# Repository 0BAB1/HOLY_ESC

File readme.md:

# HOLY ESC

My effort to bring an open source, closed loop ESC to life.

From hardware to firmware.

> This image was edited using AI to remove stickers that were bloating the image.

You can order the **FULL BUILD** in a couple of click right : (Todo : add link once project post is approved)

> [!NOTE]  
> This ESC was featured in one of my youtube videos. You may be searching for the AtMega based firmware and perfboard BOM / Schematics. I did not put these here as the design worked but is not reliable. You can open an issue if you really want it and I'll add it to some "deprecated" folder in the repo.

## THE PROJECT

The HOLY ESC is a BACK EMF based ESC, theorically able to be loaded up to 25Amps and more. But it serve educational purupses and has not be stress tested for any applications yet.

It was designed on KiCad 9 and aims at using cheap components to make the design accessible to all.

This design target drones and is planned to be tested on such applications soon.

Here are views of the PCB layers:

## Usage

### Hardware

The hardware folder contains the KiCad9 files that you can open and modify as you like for your own needs, as long as you respect the project licence at the root of this repo.

### Sofware

The sofware part is a bit more tricky.

If you get the board manufactured, you will need to load a firmware on it. In this repo, I distribute AM32 binaries made specifically for this ESC.

Here is the procedure to start spinning a motor:

**1. Connect the HOLY ESC to your host PC**

First you'll need to connect the ESC's STM32 to a host computer.

So you'll need :

- A 15V or so power supply to power the board.
- A Stlink V2 (or any clone should work as long as it has SWD)
- Download STM32CUBE programmer software

So connect the ESC to your power supply on the dedicated pads (Labeled "+" and "-" on the back of the PCB), I suggest limiting max current to 1 Amp in case a fault arises. Red LEDS should turn on, indicating a good supply of voltage into the board.

Connect the ESC SWD headers to you STLINK

And plug it into you computer.

Launch STMCUBE Programmer, click connect and it should recognze the MCU on the ESC board.

At this point you can also connect a BLDC motor on the 3 phases pads using solder (labeled A; B & C on the back of the board).

**2. Load the Firmware**

To load the firmware, you have to load a coouple things. The procedure is describe here pretty well :

[https://github-wiki-see.page/m/AlkaMotors/AM32-MultiRotor-ESC-firmware/wiki/Memory-Layout-for-flashing-with-a-St-link?utm_source=chatgpt.com](https://github-wiki-see.page/m/AlkaMotors/AM32-MultiRotor-ESC-firmware/wiki/Memory-Layout-for-flashing-with-a-St-link?utm_source=chatgpt.com)

You can use STMCube's "Erasing and Programming" tab to select a binary and load it to a specified address. Just load each binary at the right address and you should be good to go.

> To verify if you corecty modified a memory region, you can use the "Memory and File editing tab" to read a specific memory region, to check if it changed from the default values.

Bootloading and eeprom binaries are found in the page linked above. **You will find the specific binary built for this specific board in `./software/`**

> [!TIP]  
> If you are hardstuck on trying to lad a firmware, you can open an issue to get support.

Once the firmware is succesfully loaded, connect a BLDC motor to the phases pads (labeled A, B and C at the back of the PCB) using solder. Turn on your power supply (with STLINKV2 connected to PC or completely off the board to avoid asserting reset) and you should ear 3 beeps, indicating the motor is ready to armed !

Congratulations ! Now to spin a motor, you can use an arduino + voltage divider as a quick test, like I did in the video (use an LLM to write the arming sequence and speed command PWM generation) or use a servo tester / real flight controller.

> [!INFO]
> Telemetry feedback and AM32 monitoring tools not tested yet

## Future Work

- Replace the STM32F051 with a cheaper and more available package / version. (right now its 5+$ !!!! When I made the design it was like for 3-4$ MAX before going out of stock on LCSC)
- Add vias under the FETs as well. I did not initially did so to avoid assembly problems but adding a few vias on the mosfet pad should drastically increase Amperage tolerance.

## Inspirations & Thanks

A big thank you to these actors, who were a great source of inspiration in my learning and designing process !

- [The Engineering Techie](https://www.youtube.com/watch?v=1ThH9cA4eWE&t=8s)
- [Electronoobs](https://www.youtube.com/watch?v=8LXPcJD6hEA)
- [10x Aero](https://github.com/10x-Aero/ESC-Development-Board/tree/main)
- AM32 Community and posts

## Self Promotion

- The youtube channel which I featured this project on : [BRH YOUTUBE](https://www.youtube.com/@BRH_SoC)
- My Blog : [Blog Link](https://hugobrh.dev)

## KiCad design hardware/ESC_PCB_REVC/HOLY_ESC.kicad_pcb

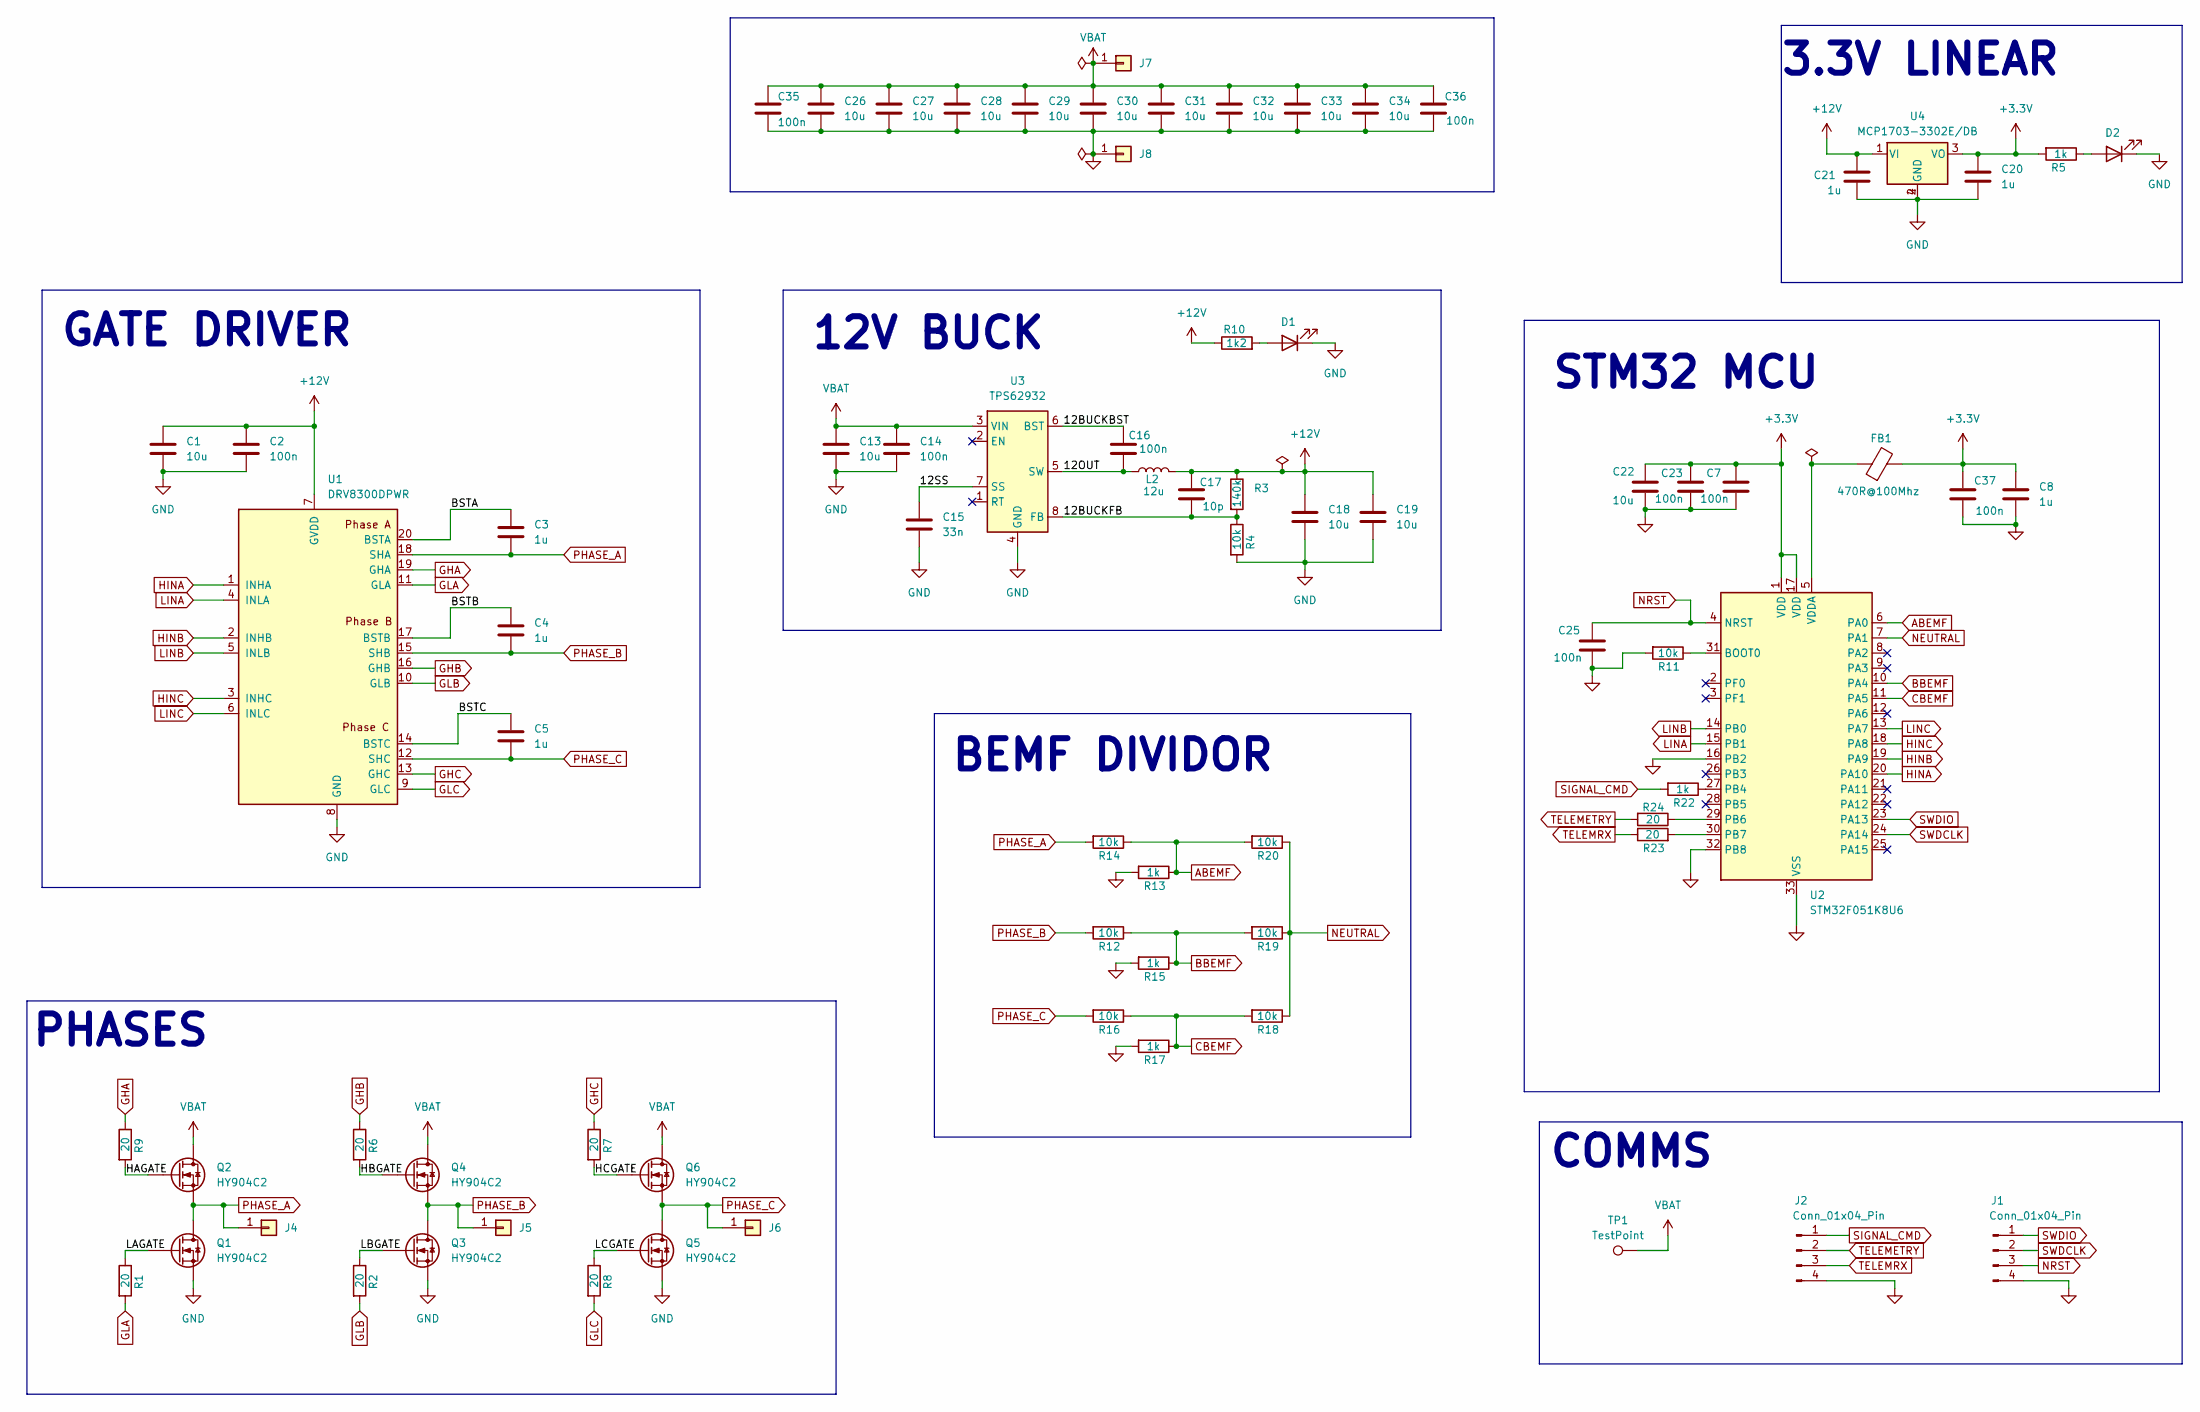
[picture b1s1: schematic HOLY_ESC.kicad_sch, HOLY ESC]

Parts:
C1, C13, C18, C19, C22, C26, C27, C28, C29, C30, C31, C32, C33, C34: 10u; C_1206_3216Metric_Pad1.33x1.80mm_HandSolder; MPN CL31A106KBHNNNE; LCSC C13585
C2, C7, C14, C16, C23, C25, C35, C36, C37: 100n; C_0603_1608Metric_Pad1.08x0.95mm_HandSolder; MPN CL10B104KB8NNNC; LCSC C1591
C3, C4, C5, C8, C20, C21: 1u; C_0805_2012Metric_Pad1.18x1.45mm_HandSolder; MPN CL21B105KBFNNNE; LCSC C28323
C15: 33n; C_0603_1608Metric_Pad1.08x0.95mm_HandSolder; MPN CL10B333KB8NNNC; LCSC C21117
C17: 10p; C_0603_1608Metric_Pad1.08x0.95mm_HandSolder; MPN CL10C100JB8NNNC; LCSC C1634
D1, D2: RED; LED_0603_1608Metric_Pad1.05x0.95mm_HandSolder; MPN YLED0603R; LCSC C19171390
FB1: 470R@100Mhz; L_0603_1608Metric_Pad1.05x0.95mm_HandSolder; MPN BLM18PG471SN1D; LCSC C97853
J1, J2: Conn_01x04_Pin; PinHeader_1x04_P2.54mm_Vertical; LCSC C32713270
J4, J5, J6, J7, J8: BatteryPad
L2: 12u; L_6.3x6.3_H3; MPN MNR6045T120MT; LCSC C20612509
Q1, Q2, Q3, Q4, Q5, Q6: HY904C2; DFN-8_L5.9-W5.2-P1.27-LS6.2-BL; MPN HY1904C2; LCSC C358116
R1, R2, R6, R7, R8, R9, R23, R24: 20; R_0603_1608Metric_Pad0.98x0.95mm_HandSolder; MPN 0603WAF200JT5E; LCSC C22950
R3: 140k; R_0603_1608Metric_Pad0.98x0.95mm_HandSolder; MPN FRC0603F1403TS; LCSC C2933144
R4, R11, R12, R14, R16, R18, R19, R20: 10k; R_0603_1608Metric_Pad0.98x0.95mm_HandSolder; MPN RT0603BRD0710KL; LCSC C95204
R5, R13, R15, R17, R22: 1k; R_0603_1608Metric_Pad0.98x0.95mm_HandSolder; MPN FRC0603F1001TS; LCSC C2907002
R10: 1k2; R_0603_1608Metric_Pad0.98x0.95mm_HandSolder; MPN FRC0603J122 TS; LCSC C2907081
TP1: TestPoint; PinHeader_1x01_P2.54mm_Vertical
U1: DRV8300DPWR; TSSOP-20_4.4x6.5mm_P0.65mm; LCSC C3036056
U2: STM32F051K8U6; QFN-32-1EP_5x5mm_P0.5mm_EP3.45x3.45mm; LCSC C72339
U3: TPS62932; SOT-583-8; MPN TPS62932DRLR; LCSC C3032935
U4: MCP1703-3302E/DB; SOT-223; MPN MCP1703-3302E/DB; LCSC C512091

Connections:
+3.3V: C7.1, C8.1, C20.1, C22.1, C23.1, C37.1, FB1.2, R5.2, U2.1 (VDD), U2.17 (VDD), U4.3 (VO)
+12V: C1.1, C2.1, C17.1, C18.1, C19.1, C21.1, L2.2, R3.1, R10.1, U1.7 (GVDD), U4.1 (VI)
/12BUCKBST: C16.1, U3.6 (BST)
/12BUCKFB: C17.2, R3.2, R4.1, U3.8 (FB)
/12OUT: C16.2, L2.1, U3.5 (SW)
/12SS: C15.1, U3.7 (SS)
/<NO NET>: FB1.1, U2.5 (VDDA)
/BSTA: C3.1, U1.20 (BSTA)
/BSTB: C4.1, U1.17 (BSTB)
/BSTC: C5.1, U1.14 (BSTC)
/HAGATE: Q2.4 (Gate), R9.2
/HBGATE: Q4.4 (Gate), R6.2
/HCGATE: Q6.4 (Gate), R7.2
/LAGATE: Q1.4 (Gate), R1.1
/LBGATE: Q3.4 (Gate), R2.1
/LCGATE: Q5.4 (Gate), R8.1
ABEMF: R13.1, R14.1, R20.2, U2.6 (PA0)
BBEMF: R12.1, R15.1, R19.2, U2.10 (PA4)
CBEMF: R16.1, R17.1, R18.2, U2.11 (PA5)
GHA: R9.1, U1.19 (GHA)
GHB: R6.1, U1.16 (GHB)
GHC: R7.1, U1.13 (GHC)
GLA: R1.2, U1.11 (GLA)
GLB: R2.2, U1.10 (GLB)
GLC: R8.2, U1.9 (GLC)
GND: C1.2, C2.2, C7.2, C8.2, C13.2, C14.2, C15.2, C18.2, C19.2, C20.2, C21.2, C22.2, C23.2, C25.2, C26.2, C27.2, C28.2, C29.2, C30.2, C31.2, C32.2, C33.2, C34.2, C35.2, C36.2, C37.2, D1.1 (K), D2.1 (K), J1.4, J2.4, J8.1, Q1.1 (Source), Q1.2 (Source), Q1.3 (Source), Q3.1 (Source), Q3.2 (Source), Q3.3 (Source), Q5.1 (Source), Q5.2 (Source), Q5.3 (Source), R4.2, R11.2, R13.2, R15.2, R17.2, U1.8 (GND), U2.16 (PB2), U2.32 (PB8), U2.33 (VSS), U3.4 (GND), U4.2 (GND), U4.4 (GND)
HINA: U1.1 (INHA), U2.20 (PA10)
HINB: U1.2 (INHB), U2.19 (PA9)
HINC: U1.3 (INHC), U2.18 (PA8)
LINA: U1.4 (INLA), U2.15 (PB1)
LINB: U1.5 (INLB), U2.14 (PB0)
LINC: U1.6 (INLC), U2.13 (PA7)
NEUTRAL: R18.1, R19.1, R20.1, U2.7 (PA1)
NRST: C25.1, J1.3, U2.4 (NRST)
unnamed: D1.2 (A), R10.2
unnamed: D2.2 (A), R5.1
unnamed: R11.1, U2.31 (BOOT0)
unnamed: R22.1, U2.27 (PB4)
unnamed: R23.1, U2.29 (PB6)
unnamed: R24.2, U2.30 (PB7)
PHASE_A: C3.2, J4.1, Q1.5 (Drain), Q1.6 (Drain), Q1.7 (Drain), Q1.8 (Drain), Q1.9 (Drain), Q2.1 (Source), Q2.2 (Source), Q2.3 (Source), R14.2, U1.18 (SHA)
PHASE_B: C4.2, J5.1, Q3.5 (Drain), Q3.6 (Drain), Q3.7 (Drain), Q3.8 (Drain), Q3.9 (Drain), Q4.1 (Source), Q4.2 (Source), Q4.3 (Source), R12.2, U1.15 (SHB)
PHASE_C: C5.2, J6.1, Q5.5 (Drain), Q5.6 (Drain), Q5.7 (Drain), Q5.8 (Drain), Q5.9 (Drain), Q6.1 (Source), Q6.2 (Source), Q6.3 (Source), R16.2, U1.12 (SHC)
SIGNAL_CMD: J2.1, R22.2
SWDCLK: J1.2, U2.24 (PA14)
SWDIO: J1.1, U2.23 (PA13)
TELEMETRY: J2.2, R23.2
TELEMRX: J2.3, R24.1
VBAT: C13.1, C14.1, C26.1, C27.1, C28.1, C29.1, C30.1, C31.1, C32.1, C33.1, C34.1, C35.1, C36.1, J7.1, Q2.5 (Drain), Q2.6 (Drain), Q2.7 (Drain), Q2.8 (Drain), Q2.9 (Drain), Q4.5 (Drain), Q4.6 (Drain), Q4.7 (Drain), Q4.8 (Drain), Q4.9 (Drain), Q6.5 (Drain), Q6.6 (Drain), Q6.7 (Drain), Q6.8 (Drain), Q6.9 (Drain), TP1.1, U3.3 (VIN)

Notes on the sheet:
GATE DRIVER
BEMF DIVIDOR
STM32 MCU
12V BUCK
PHASES
3.3V LINEAR
COMMS

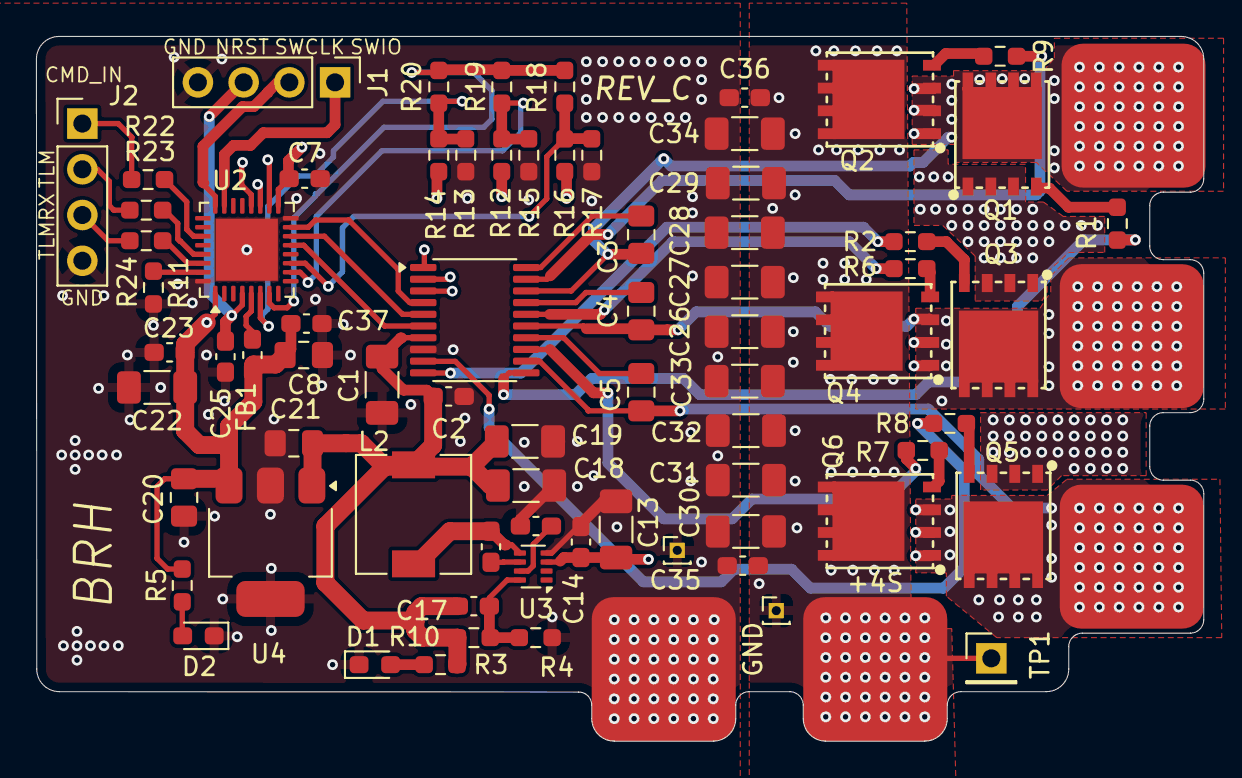
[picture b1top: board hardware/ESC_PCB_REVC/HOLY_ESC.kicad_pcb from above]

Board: 4 copper layers, 64.8 x 39.2 mm, 76 parts (0 on the bottom side), 49 nets.

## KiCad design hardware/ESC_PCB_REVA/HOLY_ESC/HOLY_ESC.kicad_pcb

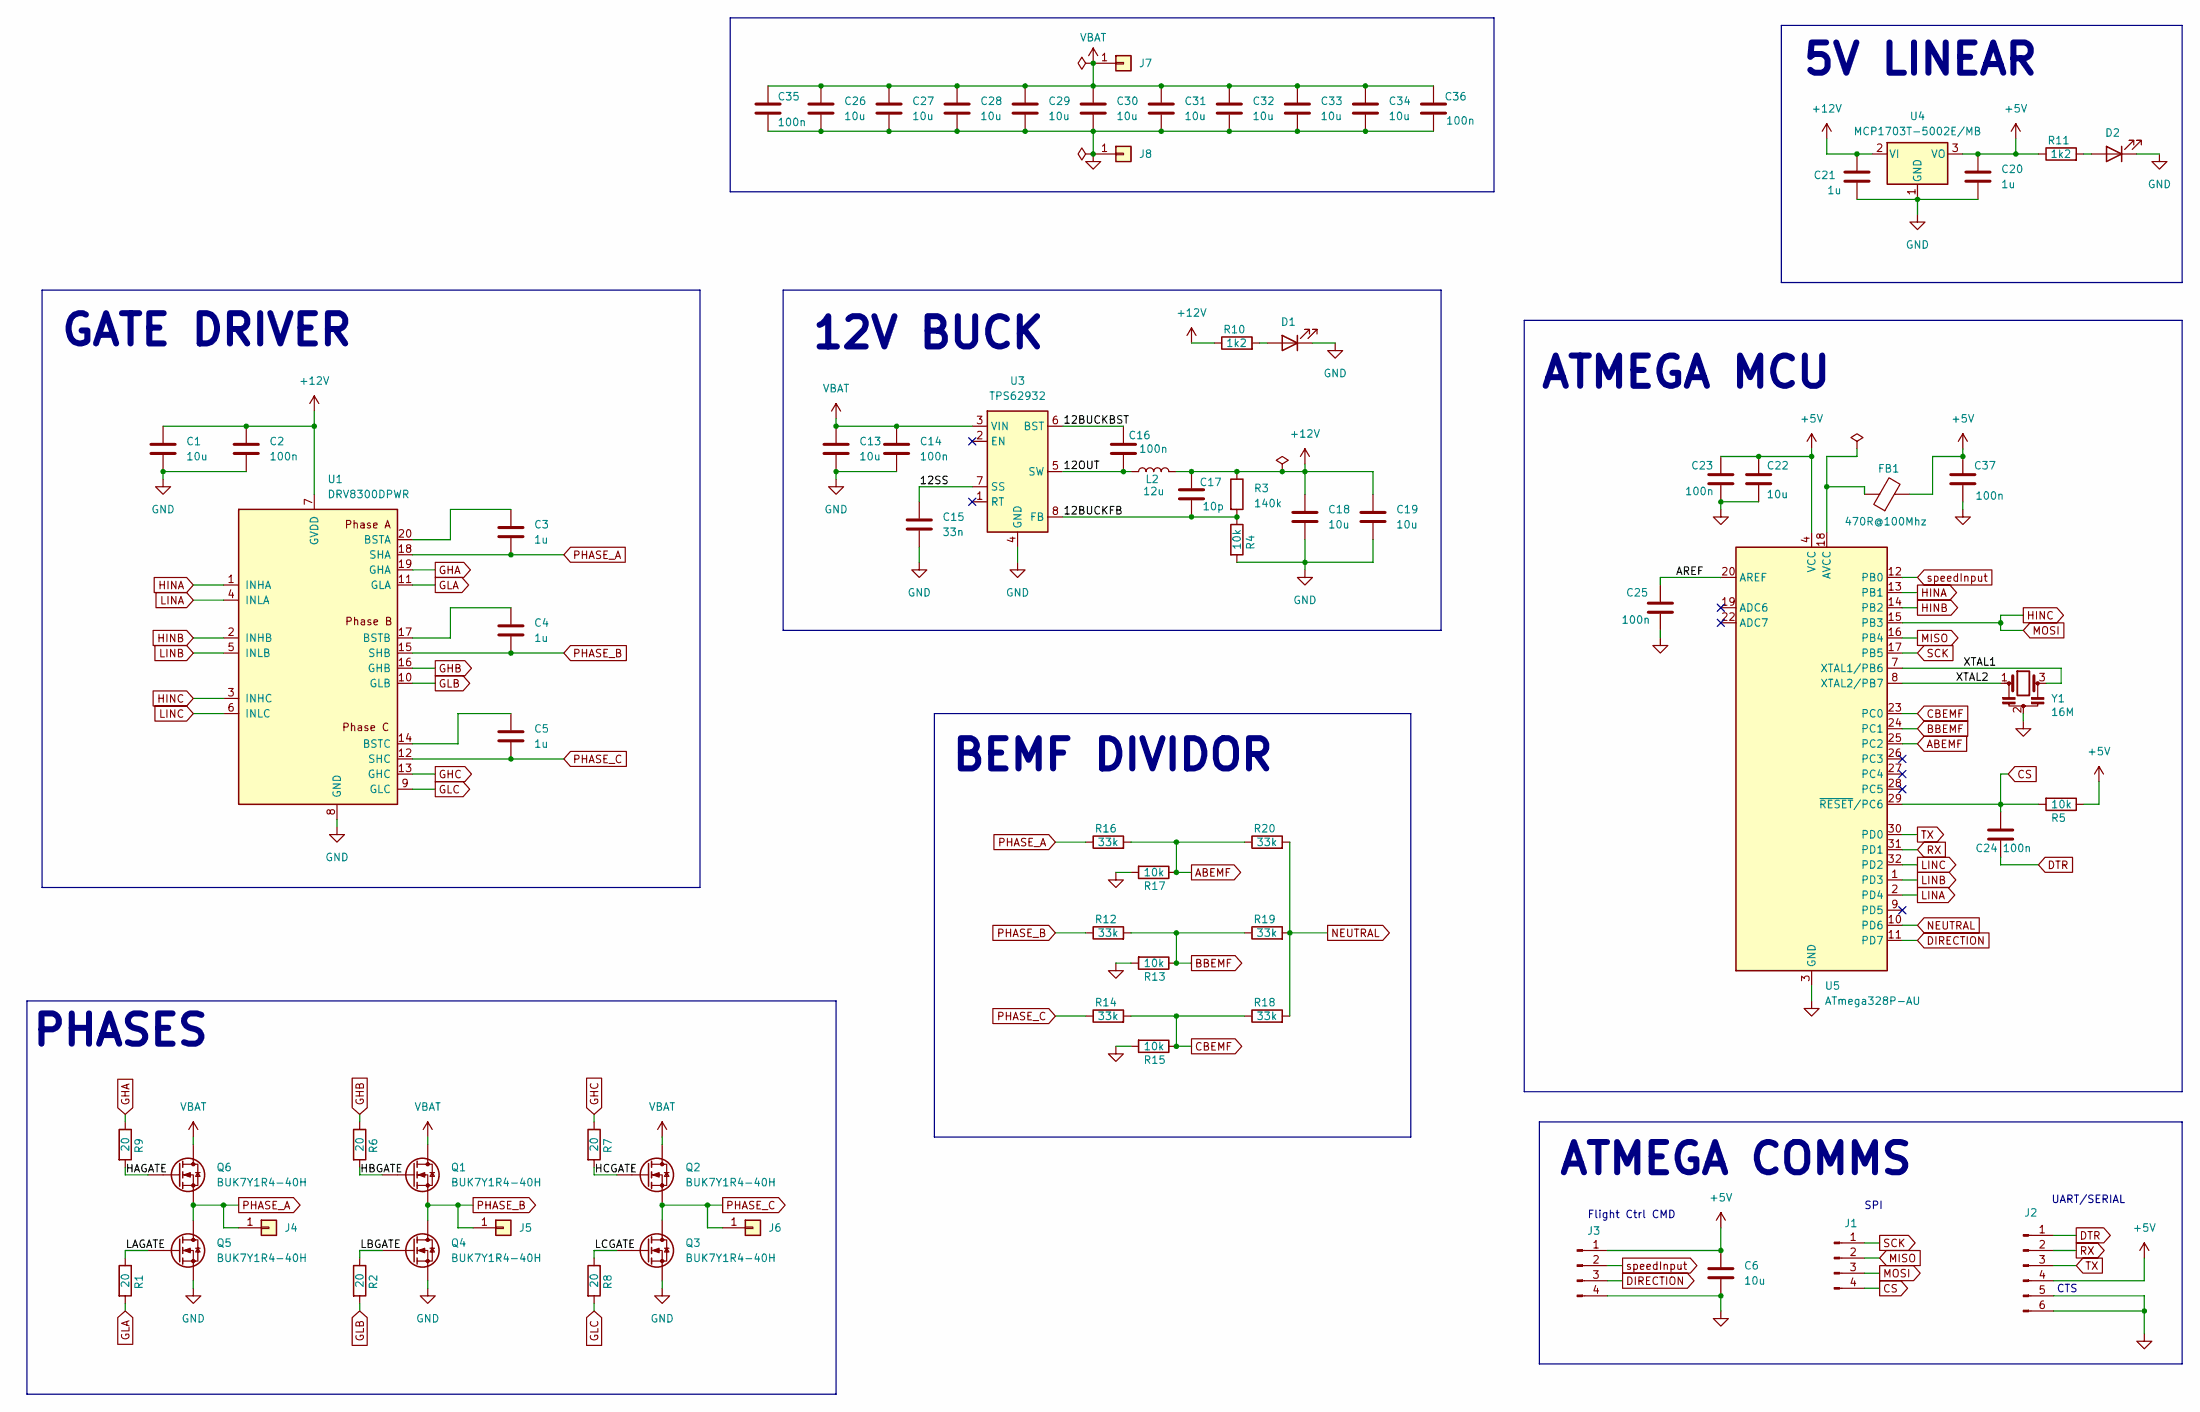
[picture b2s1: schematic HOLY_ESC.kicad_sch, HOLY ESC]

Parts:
C1, C6, C13, C18, C19, C22, C26, C27, C28, C29, C30, C31, C32, C33, C34: 10u; C_1206_3216Metric_Pad1.33x1.80mm_HandSolder; MPN CL31A106KBHNNNE; LCSC C13585
C2, C14, C16, C23, C24, C25, C35, C36, C37: 100n; C_0603_1608Metric_Pad1.08x0.95mm_HandSolder; MPN CL10B104KB8NNNC; LCSC C1591
C3, C4, C5, C20, C21: 1u; C_0805_2012Metric_Pad1.18x1.45mm_HandSolder; MPN CL21B105KBFNNNE; LCSC C28323
C15: 33n; C_0603_1608Metric_Pad1.08x0.95mm_HandSolder; MPN CL10B333KB8NNNC; LCSC C21117
C17: 10p; C_0603_1608Metric_Pad1.08x0.95mm_HandSolder; MPN CL10C100JB8NNNC; LCSC C1634
D1, D2: RED; LED_0603_1608Metric_Pad1.05x0.95mm_HandSolder; MPN YLED0603R; LCSC C19171390
FB1: 470R@100Mhz; L_0603_1608Metric_Pad1.05x0.95mm_HandSolder; MPN BLM18PG471SN1D; LCSC C97853
J1, J3: Header; PinHeader_1x04_P2.54mm_Vertical; LCSC C32713270
J2: Conn_01x06_Pin; PinHeader_1x06_P2.54mm_Vertical; LCSC C42431807
J4, J5, J6, J7, J8: BatteryPad
L2: 12u; L_6.3x6.3_H3; MPN MNR6045T120MT; LCSC C20612509
Q1, Q2, Q3, Q4, Q5, Q6: BUK7Y1R4-40H; SOT669; MPN BUK7Y1R4-40H; LCSC C6423721
R1, R2, R6, R7, R8, R9: 20; R_0603_1608Metric_Pad0.98x0.95mm_HandSolder; MPN 0603WAF200JT5E; LCSC C22950
R3: 140k; R_0603_1608Metric_Pad0.98x0.95mm_HandSolder; MPN FRC0603F1403TS; LCSC C2933144
R4, R5, R13, R15, R17: 10k; R_0603_1608Metric_Pad0.98x0.95mm_HandSolder; MPN RT0603BRD0710KL; LCSC C95204
R10, R11: 1k2; R_0603_1608Metric_Pad0.98x0.95mm_HandSolder; MPN FRC0603J122 TS; LCSC C2907081
R12, R14, R16, R18, R19, R20: 33k; R_0603_1608Metric_Pad0.98x0.95mm_HandSolder; MPN RS73F1JTTD3302B; LCSC C4009252
U1: DRV8300DPWR; TSSOP-20_4.4x6.5mm_P0.65mm; LCSC C3036056
U3: TPS62932; SOT-583-8; MPN TPS62932DRLR; LCSC C3032935
U4: MCP1703T-5002E/MB; SOT-89-3; MPN MCP1703T-5002E/MB; LCSC C27288
U5: ATmega328P-AU; TQFP-32_7x7mm_P0.8mm; MPN ATMEGA328P-AU; LCSC C14877
Y1: 16M; Resonator_SMD_Murata_CSTxExxV-3Pin_3.0x1.1mm_HandSoldering; MPN CSTNE16M0V53C000R0; LCSC C882606

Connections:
+5V: C6.1, C20.1, C22.1, C23.1, C37.1, FB1.2, J2.4, J3.1, R5.1, R11.1, U4.3 (VO), U5.4 (VCC), U5.6 (VCC)
+12V: C1.1, C2.1, C17.1, C18.1, C19.1, C21.1, L2.2, R3.1, R10.1, U1.7 (GVDD), U4.2 (VI)
/12BUCKBST: C16.1, U3.6 (BST)
/12BUCKFB: C17.2, R3.2, R4.1, U3.8 (FB)
/12OUT: C16.2, L2.1, U3.5 (SW)
/12SS: C15.1, U3.7 (SS)
/<NO NET>: FB1.1, U5.18 (AVCC)
/AREF: C25.1, U5.20 (AREF)
/HAGATE: Q6.4 (G), R9.2
/HBGATE: Q1.4 (G), R6.2
/HCGATE: Q2.4 (G), R7.2
/LAGATE: Q5.4 (G), R1.1
/LBGATE: Q4.4 (G), R2.1
/LCGATE: Q3.4 (G), R8.1
/XTAL1: U5.7 (XTAL1/PB6), Y1.3
/XTAL2: U5.8 (XTAL2/PB7), Y1.1
ABEMF: R16.2, R17.1, R20.1, U5.25 (PC2)
BBEMF: R12.2, R13.1, R19.1, U5.24 (PC1)
CBEMF: R14.2, R15.1, R18.1, U5.23 (PC0)
CS: C24.1, J1.4, R5.2, U5.29 (~RESET/PC6)
DIRECTION: J3.3, U5.11 (PD7)
DTR: C24.2, J2.1
GHA: R9.1, U1.19 (GHA)
GHB: R6.1, U1.16 (GHB)
GHC: R7.1, U1.13 (GHC)
GLA: R1.2, U1.11 (GLA)
GLB: R2.2, U1.10 (GLB)
GLC: R8.2, U1.9 (GLC)
GND: C1.2, C2.2, C6.2, C13.2, C14.2, C15.2, C18.2, C19.2, C20.2, C21.2, C22.2, C23.2, C25.2, C26.2, C27.2, C28.2, C29.2, C30.2, C31.2, C32.2, C33.2, C34.2, C35.2, C36.2, C37.2, D1.1 (K), D2.1 (K), J2.5, J2.6, J3.4, J8.1, Q3.1 (S), Q3.2 (S), Q3.3 (S), Q4.1 (S), Q4.2 (S), Q4.3 (S), Q5.1 (S), Q5.2 (S), Q5.3 (S), R4.2, R13.2, R15.2, R17.2, U1.8 (GND), U3.4 (GND), U4.1 (GND), U5.3 (GND), U5.5 (GND), U5.21 (GND), Y1.2
HINA: U1.1 (INHA), U5.13 (PB1)
HINB: U1.2 (INHB), U5.14 (PB2)
HINC: J1.3, U1.3 (INHC), U5.15 (PB3)
LINA: U1.4 (INLA), U5.2 (PD4)
LINB: U1.5 (INLB), U5.1 (PD3)
LINC: U1.6 (INLC), U5.32 (PD2)
MISO: J1.2, U5.16 (PB4)
NEUTRAL: R18.2, R19.2, R20.2, U5.10 (PD6)
unnamed: D1.2 (A), R10.2
unnamed: D2.2 (A), R11.2
unnamed: C3.1, U1.20 (BSTA)
unnamed: C4.1, U1.17 (BSTB)
unnamed: C5.1, U1.14 (BSTC)
PHASE_A: C3.2, J4.1, Q5.5 (D), Q6.1 (S), Q6.2 (S), Q6.3 (S), R16.1, U1.18 (SHA)
PHASE_B: C4.2, J5.1, Q1.1 (S), Q1.2 (S), Q1.3 (S), Q4.5 (D), R12.1, U1.15 (SHB)
PHASE_C: C5.2, J6.1, Q2.1 (S), Q2.2 (S), Q2.3 (S), Q3.5 (D), R14.1, U1.12 (SHC)
RX: J2.2, U5.31 (PD1)
SCK: J1.1, U5.17 (PB5)
TX: J2.3, U5.30 (PD0)
VBAT: C13.1, C14.1, C26.1, C27.1, C28.1, C29.1, C30.1, C31.1, C32.1, C33.1, C34.1, C35.1, C36.1, J7.1, Q1.5 (D), Q2.5 (D), Q6.5 (D), U3.3 (VIN)
speedInput: J3.2, U5.12 (PB0)

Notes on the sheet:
GATE DRIVER
BEMF DIVIDOR
UART/SERIAL
ATMEGA MCU
12V BUCK
SPI
PHASES
CTS
5V LINEAR
ATMEGA COMMS
Flight Ctrl CMD

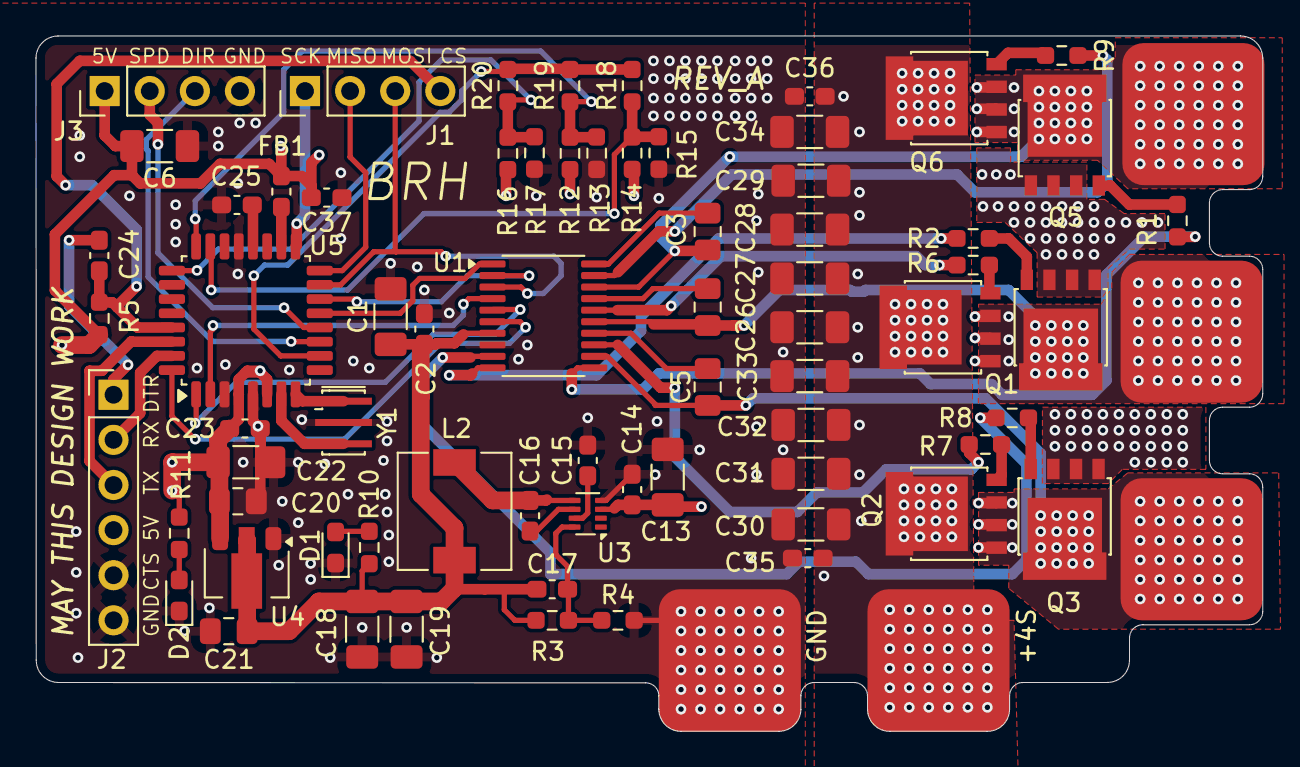
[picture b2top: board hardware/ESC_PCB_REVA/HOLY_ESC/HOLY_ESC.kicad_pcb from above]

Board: 4 copper layers, 69.1 x 39.2 mm, 74 parts (0 on the bottom side), 50 nets.

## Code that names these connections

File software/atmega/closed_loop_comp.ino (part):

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
#include <avr/io.h>

#define HINA 3
#define LINA 5
#define HINB 9
#define LINB 8
#define HINC 10
#define LINC 2

#define PHASE_A 3
#define PHASE_B 2
#define PHASE_C 1

#define DEADTIME_DELAY 2

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  // ================

  // Port D: set bits 2, 3, 6 as output
  DDRD |= (1 << PD2) | (1 << PD3) | (1 << PD5);
  // Port B: set bits 0, 1, 2 as output
  DDRB |= (1 << PB0) | (1 << PB1) | (1 << PB2);
  // all LOW initially
  PORTD = B00000000;
  PORTB = B00000000;
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
void step0(){
  // flow A to C
  PORTD = B00001100; // HINA (PD3), LINC (PD2)
  PORTB = B00000000;
}
void step01(){
  // PWM off: keep LINC
  PORTD = B00000100; // LINC (PD2)
  PORTB = B00000000;
}
void step1(){
  // flow B to C
  PORTD = B00000100; // LINC (PD2)
  PORTB = B00000010; // HINB (PB1)
}
void step11(){
  // PWM off: keep LINC
  PORTD = B00000100; // LINC (PD2)
  PORTB = B00000000;
}
void step2(){
  // flow B to A
  PORTD = B00100000; // LINA (PD5)
  PORTB = B00000010; // HINB (PB1)
}
void step21(){
  // PWM off: keep LINA
  PORTD = B00100000; // LINA (PD5)
  PORTB = B00000000;
}
void step3(){
  // flow C to A
  PORTD = B00100000; // LINA (PD5)
  PORTB = B00000100; // HINC (PB2)
}
void step31(){
  // PWM off: keep LINA
  PORTD = B00100000; // LINA (PD5)
  PORTB = B00000000;
}
void step4(){
  // flow C to B
  PORTD = B00000000;
  PORTB = B00000101; // HINC (PB2), LINB (PB0)
}
void step41(){
  // PWM off: keep LINB
  PORTD = B00000000;
  PORTB = B00000001; // LINB (PB0)
}
void step5(){
  // flow A to B
  PORTD = B00001000; // HINA (PD3)
  PORTB = B00000001; // LINB (PB0)
}
void step51(){
  // PWM off: keep LINB
  PORTD = B00000000;
  PORTB = B00000001; // LINB (PB0)
}

void loop(){
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
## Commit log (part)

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2026-06-05 Add small disclaimer
2026-06-05 Save software base
2026-06-05 Finalzed comp based sketch, still need testing as it's pretty theorical
2026-06-10 Init the repo better, still trash code though
2026-06-10 rm weird ahh file
2026-06-10 update readme layout
2026-06-25 Push REV A, prepare for REV B
2026-06-26 save REV_B first draft
2026-06-26 fix the REV A bst cap issue

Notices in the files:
software/atmega/closed_loop_comp.ino:
3-Clause BSD NON-AI License
Copyright 2025 BABIN-RIBY Hugo
